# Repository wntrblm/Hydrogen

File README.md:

# Winterbloom Hydrogen

Hydrogen is a precision buffered multiple for 1U Eurorack.

More details available at https://winterbloom.com/shop/hydrogen

## Repository layout

This repository contains the hardware design files and user guide for Hydrogen:

- **hardware/** contains the hardware design files for the mainboard and blank panel. These are all created using KiCAD.
- **user_guide/** contains the user's guide source files. These are written in Markdown and published using MkDocs.

## License and contributing

Hydrogen is open-source hardware and software, however, licensing a project like this is a little complicated. Please take a chance to review the [LICENSE](LICENSE.md) file.

We welcome contributions! Please read our [Code of Conduct](CODE_OF_CONDUCT.md) first.

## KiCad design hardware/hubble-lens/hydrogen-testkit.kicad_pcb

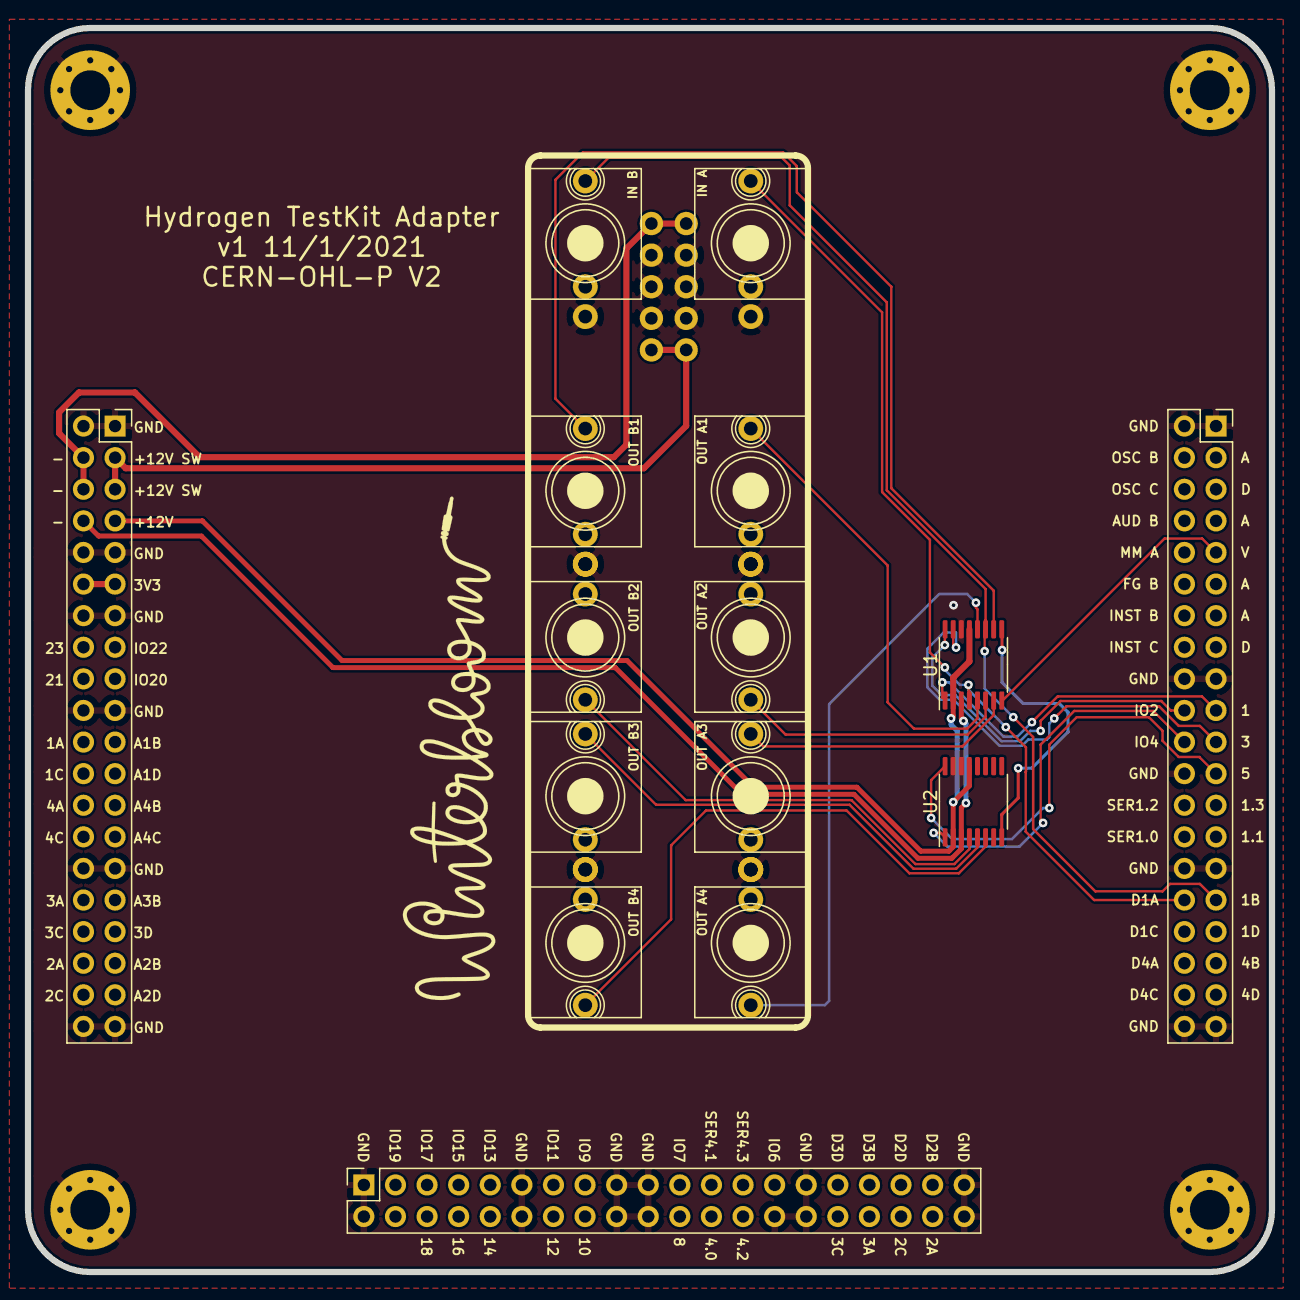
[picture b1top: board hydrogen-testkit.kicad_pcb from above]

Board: 2 copper layers, 100.0 x 100.0 mm, 20 parts (1 on the bottom side), 23 nets.

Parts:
BB1: Left; PinSocket_2x20_P2.54mm_Vertical
BB2: Bottom; PinSocket_2x20_P2.54mm_Vertical
BB3: Right; PinSocket_2x20_P2.54mm_Vertical
H1, H2, H3, H4: M3; MountingHole_3.2mm_M3_Pad_Via
J1: Power; Eurorack_Power
J2: IN A; WQP-WQP518MA-skinny
J3: OUT A1; WQP-WQP518MA-skinny
J4: OUT A2; WQP-WQP518MA-skinny
J5: OUT A3; WQP-WQP518MA-skinny
J6: OUT A4; WQP-WQP518MA-skinny
J7: IN B; WQP-WQP518MA-skinny
J8: OUT B1; WQP-WQP518MA-skinny
J9: OUT B2; WQP-WQP518MA-skinny
J10: OUT B3; WQP-WQP518MA-skinny
J11: OUT B4; WQP-WQP518MA-skinny
U1, U2: MUX508; TSSOP-16_4.4x5mm_P0.65mm

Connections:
+3V3: BB1.11, BB1.12
+12V: BB1.7, U1.2, U1.13, U2.2, U2.13
+12VDOWNSTREAM: BB1.3, BB1.5, J1.1, J1.2
-12V: BB1.8, U1.3, U2.3
-12VDOWNSTREAM: BB1.4, BB1.6, J1.9, J1.10
/DAC_1A: BB3.32, J2.T, U1.4
/DAC_1B: BB3.31, J7.T, U1.11
/EXT_MM_V: BB3.9, U1.8
/IO1: BB3.19, U1.1
/IO2: BB3.20, U1.16
/IO3: BB3.21, U1.15
/IO4: BB3.22, U2.1
/IO5: BB3.23, U2.16
/OUT_A1: J3.T, U1.5
/OUT_A2: J4.T, U1.6
/OUT_A3: J5.T, U1.7
/OUT_A4: J6.T, U1.12
/OUT_B1: J8.T, U1.10
/OUT_B2: J9.T, U2.4
/OUT_B3: J10.T, U2.5
/OUT_B4: J11.T, U2.6
GND: BB1.1, BB1.2, BB1.9, BB1.10, BB1.13, BB1.14, BB1.19, BB1.20, BB1.29, BB1.30, BB1.39, BB1.40, BB2.1, BB2.2, BB2.11, BB2.12, BB2.17, BB2.18, BB2.19, BB2.20, BB2.28, BB2.29, BB2.30, BB2.39, BB2.40, BB3.1, BB3.2, BB3.17, BB3.18, BB3.24, BB3.29, BB3.30, BB3.39, BB3.40, H1.1, H2.1, H3.1, H4.1, J1.3, J1.4, J1.5, J1.6, J1.7, J1.8, J2.S, J3.S, J4.S, J5.S, J6.S, J7.S, J8.S, J9.S, J10.S, J11.S, U1.14, U2.14, U2.15
unnamed: U1.9, U2.8

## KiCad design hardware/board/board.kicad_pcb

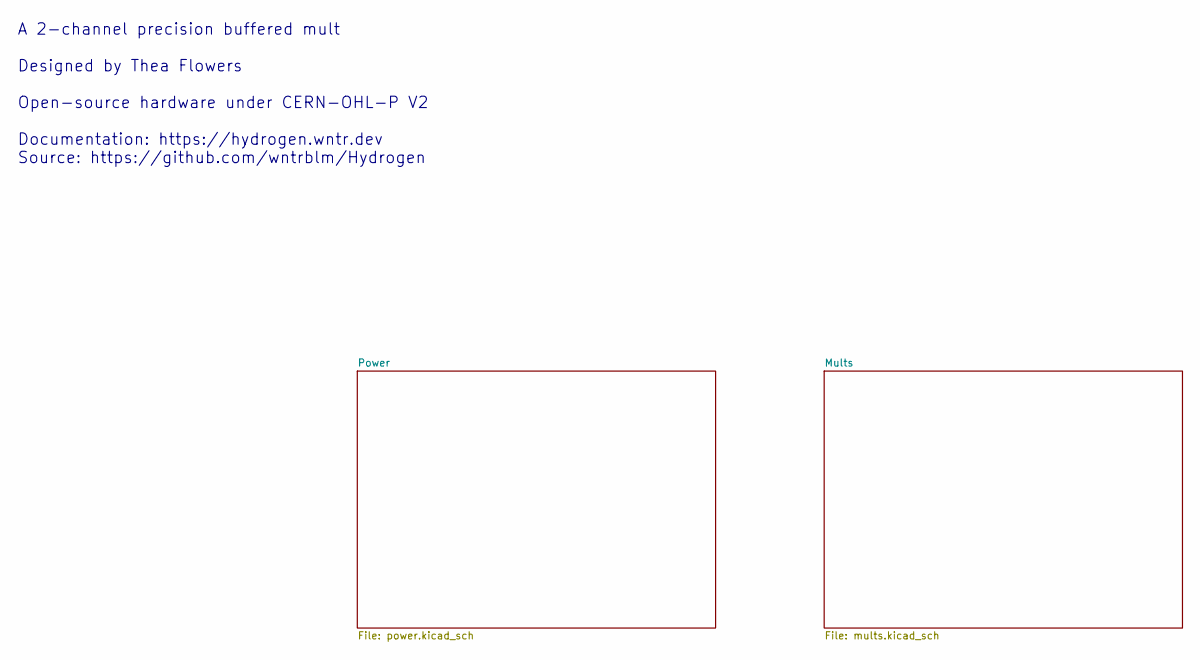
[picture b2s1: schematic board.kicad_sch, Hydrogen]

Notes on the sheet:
A 2-channel precision buffered mult Designed by Thea Flowers Open-source hardware under CERN-OHL-P V2 Documentation: https://hydrogen.wntr.dev Source: https://github.com/wntrblm/Hydrogen

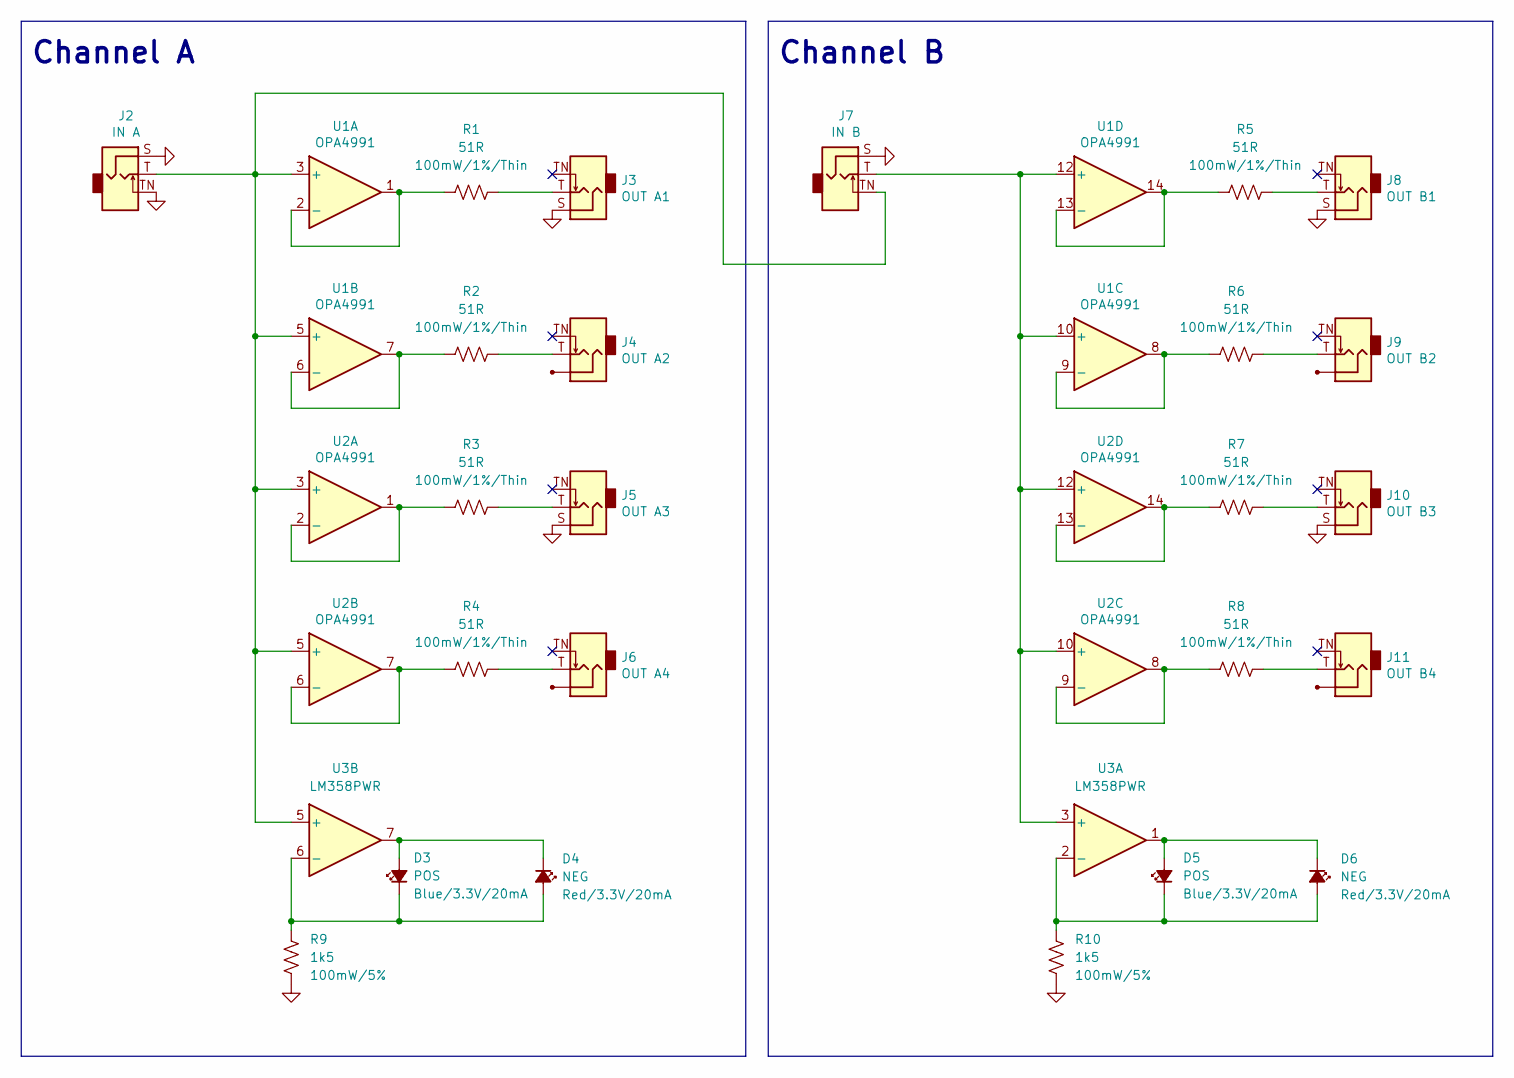
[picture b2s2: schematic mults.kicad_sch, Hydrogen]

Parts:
D3, D5: POS; LED_0805_Kingbright_APT2012; Rating Blue/3.3V/20mA; MPN APT2012VBC/D; DigiKey 754-1794-1-ND
D4, D6: NEG; LED_0805_Kingbright_APT2012; Rating Red/3.3V/20mA; MPN APT2012SURCK; DigiKey 754-1133-1-ND
J2: IN A; AudioJack_WQP518MA_Compact_S
J3: OUT A1; AudioJack_WQP518MA_Compact_S
J4: OUT A2; AudioJack_WQP518MA_No_S
J5: OUT A3; AudioJack_WQP518MA_Compact_S
J6: OUT A4; AudioJack_WQP518MA_No_S
J7: IN B; AudioJack_WQP518MA_Compact_S
J8: OUT B1; AudioJack_WQP518MA_Compact_S
J9: OUT B2; AudioJack_WQP518MA_No_S
J10: OUT B3; AudioJack_WQP518MA_Compact_S
J11: OUT B4; AudioJack_WQP518MA_No_S
R1, R2, R3, R4, R5, R6, R7, R8: 51R; R_0603_HandSolder; Rating 100mW/1%/Thin; MPN RT0603FRE0751RL; DigiKey 13-RT0603FRE0751RLCT-ND
R9, R10: 1k5; R_0603_HandSolder; Rating 100mW/5%; MPN RC0603JR-071K5L; DigiKey 311-1.5KGRCT-ND
U1, U2: OPA4991; TSSOP-14_4.4x5mm_P0.65mm; MPN OPA4991IPWR; Mouser 595-OPA4991IPWR
U3: LM358PWR; TSSOP-8_4.4x3mm_P0.65mm; MPN LM358PWR; DigiKey 296-OPA4991IPWRCT-ND

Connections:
GND: J2.S (Sleeve), J2.TN (Tip_normalize), J3.S (Sleeve), J5.S (Sleeve), J7.S (Sleeve), J8.S (Sleeve), J10.S (Sleeve), R9.1, R10.1; also elsewhere on the board
unnamed: D3.2 (A), D4.1 (K), U3.7
unnamed: D3.1 (K), D4.2 (A), R9.2, U3.6 (-)
unnamed: D5.2 (A), D6.1 (K), U3.1
unnamed: D5.1 (K), D6.2 (A), R10.2, U3.2 (-)
unnamed: J2.T (Tip), J7.TN (Tip_normalize), U1.3 (+), U1.5 (+), U2.3 (+), U2.5 (+), U3.5 (+)
unnamed: J3.T (Tip), R1.1
unnamed: J4.T (Tip), R2.1
unnamed: J5.T (Tip), R3.1
unnamed: J6.T (Tip), R4.1
unnamed: J7.T (Tip), U1.10 (+), U1.12 (+), U2.10 (+), U2.12 (+), U3.3 (+)
unnamed: J8.T (Tip), R5.1
unnamed: J9.T (Tip), R6.1
unnamed: J10.T (Tip), R7.1
unnamed: J11.T (Tip), R8.1
unnamed: R1.2, U1.1, U1.2 (-)
unnamed: R2.2, U1.6 (-), U1.7
unnamed: R6.2, U1.8, U1.9 (-)
unnamed: R5.2, U1.13 (-), U1.14
unnamed: R3.2, U2.1, U2.2 (-)
unnamed: R4.2, U2.6 (-), U2.7
unnamed: R8.2, U2.8, U2.9 (-)
unnamed: R7.2, U2.13 (-), U2.14

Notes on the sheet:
Channel A
Channel B

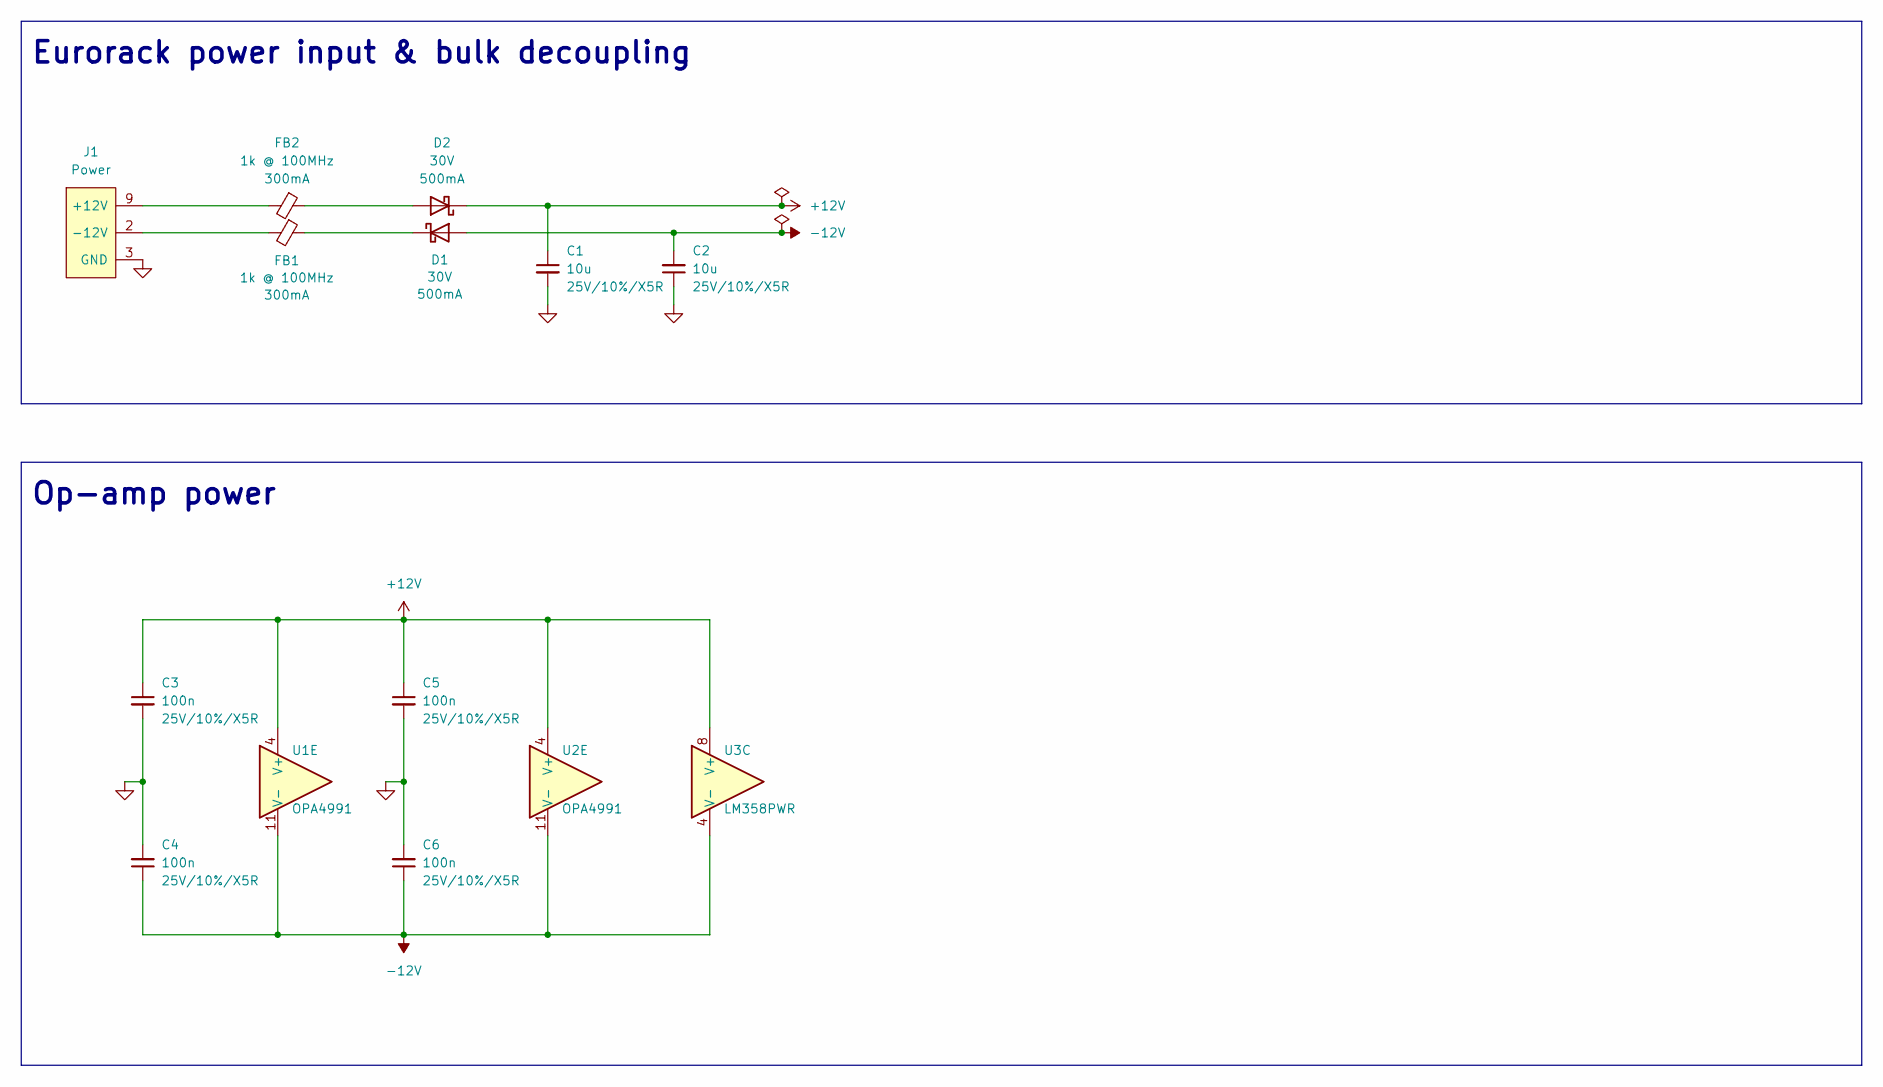
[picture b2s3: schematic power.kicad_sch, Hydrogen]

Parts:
C1, C2: 10u; C_0805_HandSolder; Rating 25V/10%/X5R; MPN GRM21BR61E106KA73K; DigiKey 490-16824-1-ND
C3, C4, C5, C6: 100n; C_0603_HandSolder; Rating 25V/10%/X5R; MPN CL10B104KB8NNNC; DigiKey 1276-1000-2-ND
D1, D2: 30V; D_SOD-123+SOD-123F; Rating 500mA; MPN PMEG2005EGWX; DigiKey 1727-7329-1-ND
FB1, FB2: 1k @ 100MHz; L_0603_HandSolder; Rating 300mA; MPN BLM18AG102SN1D; DigiKey 490-1015-1-ND
J1: Power; Eurorack_Power_2x5_Shrouded_Lock; MPN 302-S101; DigiKey ED1543-ND
U1, U2: OPA4991; TSSOP-14_4.4x5mm_P0.65mm; MPN OPA4991IPWR; Mouser 595-OPA4991IPWR
U3: LM358PWR; TSSOP-8_4.4x3mm_P0.65mm; MPN LM358PWR; DigiKey 296-OPA4991IPWRCT-ND

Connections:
+12V: C1.1, C3.1, C5.1, D2.1 (K), U1.4 (V+), U2.4 (V+), U3.8 (V+)
-12V: C2.2, C4.1, C6.1, D1.2 (A), U1.11 (V-), U2.11 (V-), U3.4 (V-)
GND: C1.2, C2.1, C3.2, C4.2, C5.2, C6.2, J1.3 (GND), J1.4 (GND), J1.5 (GND), J1.6 (GND), J1.7 (GND), J1.8 (GND); also elsewhere on the board
unnamed: D1.1 (K), FB1.1
unnamed: D2.2 (A), FB2.1
unnamed: FB1.2, J1.1 (-12V), J1.2 (-12V)
unnamed: FB2.2, J1.9 (+12V), J1.10 (+12V)

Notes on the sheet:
Eurorack power input & bulk decoupling
Op-amp power

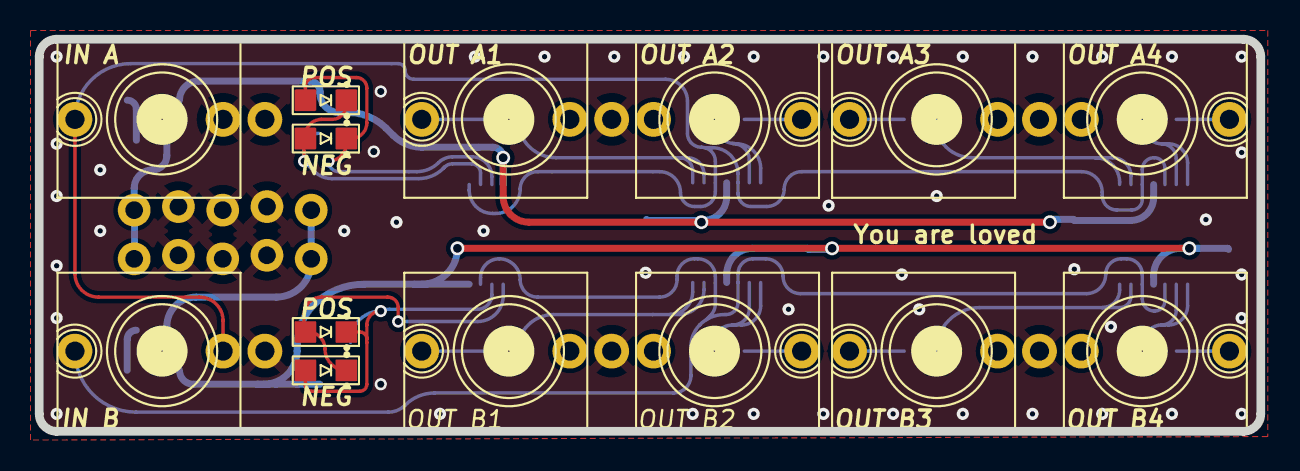
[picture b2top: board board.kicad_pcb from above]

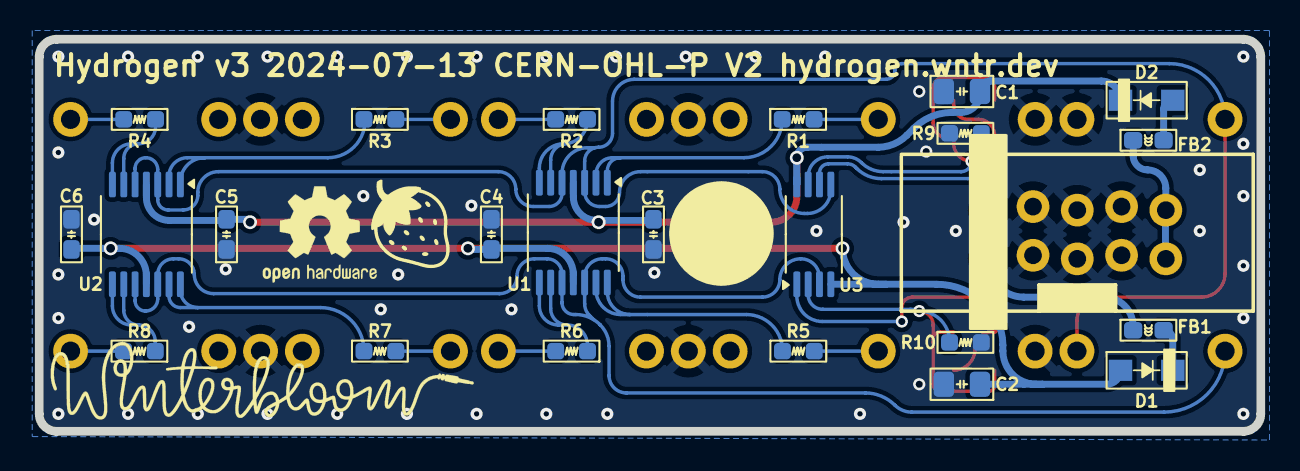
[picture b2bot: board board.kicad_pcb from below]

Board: 2 copper layers, 70.1 x 22.5 mm, 38 parts (24 on the bottom side), 29 nets.

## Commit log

2021-11-08 Remove Helium's files
2021-11-08 Move Hydrogen files into hardware/
2021-11-08 Add readme, license, etc.
2021-11-08 Add testkit adapter
2021-11-08 Update resistor values; create PDF
2021-11-08 Add user guide
2021-11-08 Fix link
2021-11-16 Update resistor values
2021-11-16 Update specs in user guide
2021-12-08 hardware: add laser design's for the testkit adapter board guide, pin holder, and pressure plate
2021-12-23 user guide: add basic functionality for the surface mount assembly guide
2021-12-23 hardware: add data to schematic for showing parts in the surface mount assembly guide
2021-12-23 factory: add factory setup script
2021-12-25 user guide: add surface mount assembly guide
2021-12-25 user guide: note that the ic mark can be a circle or a star
2021-12-25 user guide: some small accessibility fixes
2021-12-25 user guide: move pcbassembly stuff into theme, fixup some stuff.
2021-12-28 Migrate to KiCAD 6, fix flipped C2
2021-12-28 Remove old KiCAD 5 files
2021-12-28 hardware: update PDF of schematic
2021-12-29 user guide: add module usage section
2021-12-30 user guide: fix OSHW mark
2021-12-30 user guide: don't unnecessarily use a list
2022-01-07 user guide: Add through hole kit build guide
2022-01-08 user guide: fix small typo in build guide
2022-01-11 factory: use wintertools' built in printing functionality
2022-01-25 hardware: update page layout to Winterbloom's standard layout
2022-02-03 user guide: add oshw certification
2022-02-03 user guide: fix link to oshw certification lol
2022-02-03 meta: automatically publish user guide when changes are pushed
2022-06-19 user guide: link to assembled and kit product pages
2022-06-19 Deployed dae3995 with MkDocs version: 1.3.0
2023-01-17 Add design files for light guide
2024-02-23 user guide: Switch over to Wintersong theme, remove surface mount kit guide
2024-02-23 meta: update docs build github action
2024-02-23 user guide: update requirements.txt
2024-02-23 Deployed 01738dc with MkDocs version: 1.5.3
2024-07-14 Board revision 3
    Schematic:
    - Migrated to new Winterbloom page layout
    - Split into power and mult schematics
    - Updated all symbols
    - Added sourcing information for all items
    PCB:
2024-07-14 hardware: add faceplate
2024-07-14 hardware: rename testkit-adapter to hubble-lens
